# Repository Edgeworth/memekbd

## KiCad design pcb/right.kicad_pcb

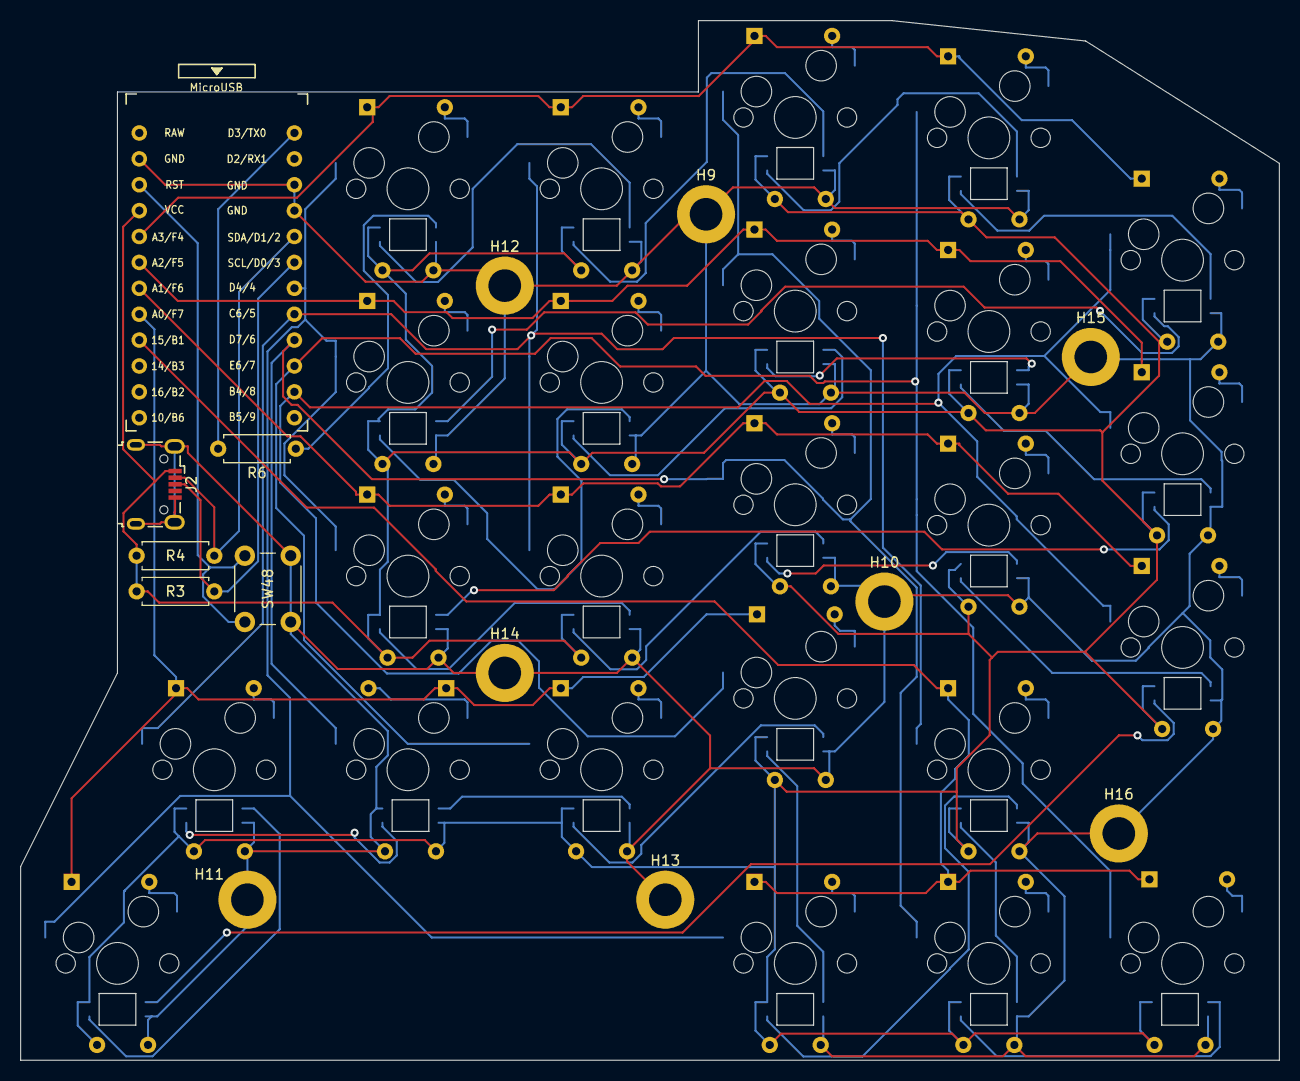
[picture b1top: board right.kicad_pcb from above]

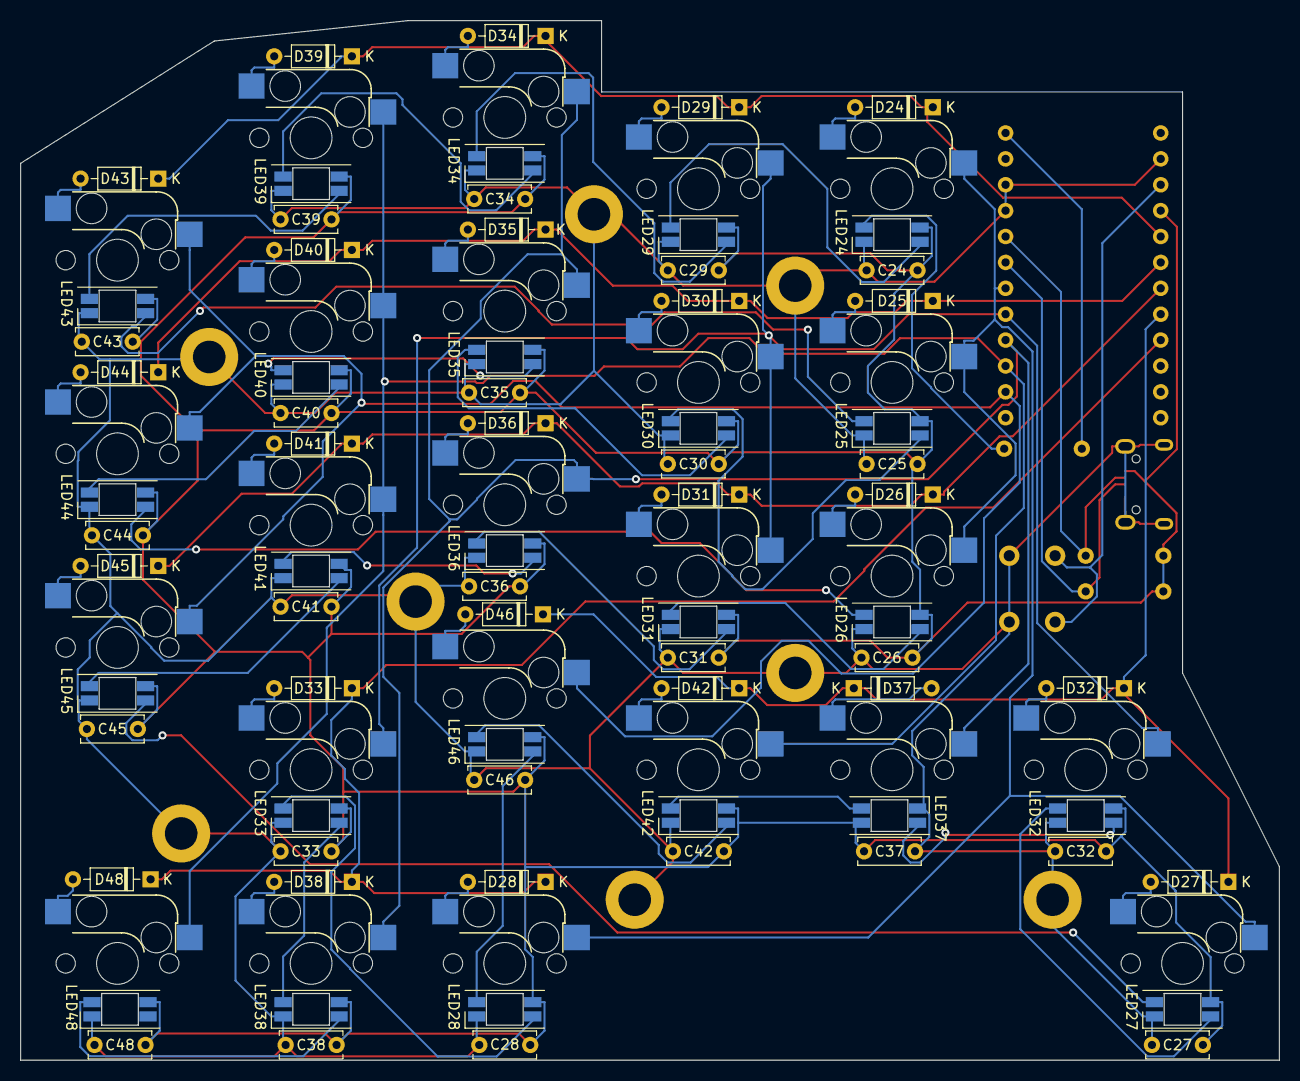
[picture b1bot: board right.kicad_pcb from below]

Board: 2 copper layers, 123.5 x 102.0 mm, 110 parts (72 on the bottom side), 64 nets.

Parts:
C24, C25, C26, C27, C28, C29, C30, C31, C32, C33, C34, C35, C36, C37, C38, C39, C40, C41, C42, C43, C44, C45, C46, C48: 0.1uF; C_Disc_D6.0mm_W2.5mm_P5.00mm
D24, D25, D26, D27, D28, D29, D30, D31, D32, D33, D34, D35, D36, D37, D38, D39, D40, D41, D42, D43, D44, D45, D46, D48: 1N4148; D_DO-35_SOD27_P7.62mm_Horizontal
H9, H10, H11, H12, H13, H14, H15, H16: MountingHole_Pad; MountingHole_3.2mm_M3_ISO7380_Pad
J2: USB_B_Micro; USB_Micro-B_Wuerth_629105150521
LED24, LED25, LED26, LED27, LED28, LED29, LED30, LED31, LED32, LED33, LED34, LED35, LED36, LED37, LED38, LED39, LED40, LED41, LED42, LED43, LED44, LED45, LED46, LED48: YS-SK6812MINI-E
R3, R4: 10k; R_Axial_DIN0207_L6.3mm_D2.5mm_P7.62mm_Horizontal
R6: 1k; R_Axial_DIN0207_L6.3mm_D2.5mm_P7.62mm_Horizontal
SW24, SW25, SW26, SW27, SW28, SW29, SW30, SW31, SW32, SW33, SW34, SW35, SW36, SW37, SW38, SW39, SW40, SW41, SW42, SW43, SW44, SW45, SW46, SW50: SW_Push; CherryMX_Hotswap
SW48: SW_Push; SW_PUSH_6mm_H7.3mm
U2: ProMicro; ProMicro_v3.5

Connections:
+5V: C24.1, C25.1, C26.1, C27.1, C28.1, C29.1, C30.1, C31.1, C32.1, C33.1, C34.1, C35.1, C36.1, C37.1, C38.1, C39.1, C40.1, C41.1, C42.1, C43.1, C44.1, C45.1, C46.1, C48.1, J2.1 (VBUS), LED24.1 (VDD), LED25.1 (VDD), LED26.1 (VDD), LED27.1 (VDD), LED28.1 (VDD), LED29.1 (VDD), LED30.1 (VDD), LED31.1 (VDD), LED32.1 (VDD), LED33.1 (VDD), LED34.1 (VDD), LED35.1 (VDD), LED36.1 (VDD), LED37.1 (VDD), LED38.1 (VDD), LED39.1 (VDD), LED40.1 (VDD), LED41.1 (VDD), LED42.1 (VDD), LED43.1 (VDD), LED44.1 (VDD), LED45.1 (VDD), LED46.1 (VDD), LED48.1 (VDD), R3.2, R4.2, U2.21 (VCC)
/rLED: R6.2, U2.1 (TX0/D3)
/rRST: SW48.1, U2.22 (RST)
/rSCL: J2.3 (D+), R3.1, U2.6 (3/D0/SCL)
/rSDA: J2.2 (D-), R4.1, U2.5 (2/D1/SDA)
/rcol0: SW24.1, SW25.1, SW26.1, SW27.1, SW28.1, U2.7 (4/D4)
/rcol1: SW29.1, SW30.1, SW31.1, SW32.1, SW33.1, U2.8 (5/C6)
/rcol2: SW34.1, SW35.1, SW36.1, SW37.1, SW38.1, U2.9 (6/D7)
/rcol3: SW39.1, SW40.1, SW41.1, SW42.1, SW50.1, U2.10 (7/E6)
/rcol4: SW43.1, SW44.1, SW45.1, SW46.1, U2.11 (8/B4)
/rrow0: D24.1 (K), D29.1 (K), D34.1 (K), D39.1 (K), D43.1 (K), U2.20 (F4/A3)
/rrow1: D25.1 (K), D30.1 (K), D35.1 (K), D40.1 (K), D44.1 (K), U2.19 (F5/A2)
/rrow2: D26.1 (K), D31.1 (K), D36.1 (K), D41.1 (K), D45.1 (K), U2.18 (F6/A1)
/rrow3: D27.1 (K), D32.1 (K), D37.1 (K), D42.1 (K), D46.1 (K), U2.17 (F7/A0)
/rrow4: D28.1 (K), D33.1 (K), D38.1 (K), D48.1 (K), U2.16 (B1/15)
GND: C24.2, C25.2, C26.2, C27.2, C28.2, C29.2, C30.2, C31.2, C32.2, C33.2, C34.2, C35.2, C36.2, C37.2, C38.2, C39.2, C40.2, C41.2, C42.2, C43.2, C44.2, C45.2, C46.2, C48.2, H9.1, H10.1, H11.1, H12.1, H13.1, H14.1, H15.1, H16.1, J2.5 (GND), J2.6 (Shield), LED24.3 (VSS), LED25.3 (VSS), LED26.3 (VSS), LED27.3 (VSS), LED28.3 (VSS), LED29.3 (VSS), LED30.3 (VSS), LED31.3 (VSS), LED32.3 (VSS), LED33.3 (VSS), LED34.3 (VSS), LED35.3 (VSS), LED36.3 (VSS), LED37.3 (VSS), LED38.3 (VSS), LED39.3 (VSS), LED40.3 (VSS), LED41.3 (VSS), LED42.3 (VSS), LED43.3 (VSS), LED44.3 (VSS), LED45.3 (VSS), LED46.3 (VSS), LED48.3 (VSS), SW48.2, U2.3 (GND), U2.4 (GND), U2.23 (GND)
unnamed: D24.2 (A), SW24.2
unnamed: D25.2 (A), SW25.2
unnamed: D26.2 (A), SW26.2
unnamed: D27.2 (A), SW27.2
unnamed: D28.2 (A), SW28.2
unnamed: D29.2 (A), SW29.2
unnamed: D30.2 (A), SW30.2
unnamed: D31.2 (A), SW31.2
unnamed: D32.2 (A), SW32.2
unnamed: D33.2 (A), SW33.2
unnamed: D34.2 (A), SW34.2
unnamed: D35.2 (A), SW35.2
unnamed: D36.2 (A), SW36.2
unnamed: D37.2 (A), SW37.2
unnamed: D38.2 (A), SW38.2
unnamed: D39.2 (A), SW39.2
unnamed: D40.2 (A), SW40.2
unnamed: D41.2 (A), SW41.2
unnamed: D42.2 (A), SW42.2
unnamed: D43.2 (A), SW43.2
unnamed: D44.2 (A), SW44.2
unnamed: D45.2 (A), SW45.2
unnamed: D46.2 (A), SW46.2
unnamed: D48.2 (A), SW50.2
unnamed: LED24.2 (DOUT), LED29.4 (DIN)
unnamed: LED24.4 (DIN), R6.1
unnamed: LED25.2 (DOUT), LED30.4 (DIN)
unnamed: LED25.4 (DIN), LED43.2 (DOUT)
unnamed: LED26.2 (DOUT), LED31.4 (DIN)
unnamed: LED26.4 (DIN), LED44.2 (DOUT)
unnamed: LED27.2 (DOUT), LED32.4 (DIN)
unnamed: LED27.4 (DIN), LED45.2 (DOUT)
unnamed: LED28.2 (DOUT), LED33.4 (DIN)
unnamed: LED28.4 (DIN), LED46.2 (DOUT)
unnamed: LED29.2 (DOUT), LED34.4 (DIN)
unnamed: LED30.2 (DOUT), LED35.4 (DIN)
unnamed: LED31.2 (DOUT), LED36.4 (DIN)
unnamed: LED32.2 (DOUT), LED37.4 (DIN)
unnamed: LED33.2 (DOUT), LED38.4 (DIN)
unnamed: LED34.2 (DOUT), LED39.4 (DIN)
unnamed: LED35.2 (DOUT), LED40.4 (DIN)
unnamed: LED36.2 (DOUT), LED41.4 (DIN)
unnamed: LED37.2 (DOUT), LED42.4 (DIN)
unnamed: LED38.2 (DOUT), LED48.4 (DIN)
unnamed: LED39.2 (DOUT), LED43.4 (DIN)
unnamed: LED40.2 (DOUT), LED44.4 (DIN)
unnamed: LED41.2 (DOUT), LED45.4 (DIN)
unnamed: LED42.2 (DOUT), LED46.4 (DIN)
